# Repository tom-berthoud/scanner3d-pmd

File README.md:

# Scanner 3D — donner une forme numérique au réel

<p align="center">
  <strong>Un scanner 3D open source, compact et low-cost, conçu autour d'un Raspberry Pi.</strong><br>
  Numérisez un objet, reconstruisez sa géométrie et exportez un modèle STL prêt à être réutilisé.
</p>

<p align="center">
  <a href="assets/photo/poster_Scanner_3D.pdf">Voir le poster du projet</a> ·
  <a href="docs/rapport/">Lire le rapport complet</a>
</p>

---

## Le projet en une phrase

Scanner 3D transforme un objet posé sur un plateau rotatif en un modèle numérique exploitable grâce à une ligne laser, deux caméras et une chaîne logicielle complète — de la capture au maillage STL.

## De l'objet au modèle 3D

1. L'objet est placé au centre du plateau.
2. Le plateau effectue une rotation progressive sur 360°.
3. À chaque position, le laser dessine un profil lumineux et les deux caméras capturent la scène.
4. La ligne laser est détectée puis convertie en profil 3D par triangulation.
5. Les profils sont fusionnés en nuage de points, filtrés et transformés en maillage.
6. Le résultat est visualisable dans l'interface et exportable en STL ou OBJ.

## Pourquoi ce scanner ?

- **Accessible** — une architecture low-cost pensée pour un budget d'environ 300 CHF.
- **Autonome** — boîtier fermé, plateau motorisé, laser, caméras et écran tactile réunis dans un seul système.
- **Pédagogique** — mécanique, électronique, vision, géométrie 3D et interface web dans un même projet.
- **Pratique** — un parcours de scan simple, avec aperçu, suivi de progression et téléchargement du résultat.
- **Reproductible** — configuration YAML, calibration guidée, simulation hardware et tests automatisés.

## Une architecture complète

| Couche | Rôle |
| --- | --- |
| **Acquisition** | Capture synchronisée des deux caméras et commande du laser |
| **Vision** | Détection robuste de la ligne laser et réduction du bruit |
| **Géométrie** | Calibration caméra / laser, triangulation et fusion des deux vues |
| **Reconstruction** | Assemblage des profils en nuage de points puis maillage |
| **Interface** | Pilotage web, aperçu caméra, progression en temps réel et viewer 3D |
| **Matériel** | Raspberry Pi, moteur pas à pas, plateau rotatif, double caméra et écran local |

## Résultats

Le prototype répond aux objectifs du projet :

- acquisition d'un profil 3D à chaque rotation ;
- fusion des profils en nuage de points ;
- génération d'un maillage STL imprimable ;
- pilotage depuis une interface web Raspberry Pi ;
- fonctionnement dans une boîte fermée pour maîtriser la lumière ambiante ;
- objets ciblés jusqu'à environ **150 × 150 × 150 mm** et scan visé en moins de **10 minutes**.

Les raccourcis de déploiement, la calibration, le lancement sur Raspberry Pi et les routes de l'API sont documentés dans [README-technique.md](README-technique.md).

## Explorer les ressources

- [Poster de présentation](assets/photo/poster_Scanner_3D.pdf) — la synthèse visuelle du projet.
- [Rapport complet](docs/rapport/) — conception mécanique, électronique, logicielle et résultats.
- [Conception mécanique](docs/conceptionmecanique/) — pièces, assemblages, DXF et STL.
- [Schéma électronique](docs/schema/) — schéma et PCB KiCad.
- [Procédure de connexion](docs/connection_procedure.md) — relier le PC au Raspberry Pi.
- [Assets du projet](assets/photo/) — photos du prototype, captures d'écran et résultats 3D.

## L'équipe

Projet multidisciplinaire PMD — HEIG-VD, 2026

**[Tom Berthoud](https://github.com/tom-berthoud) · [Jason Weber](https://github.com/Jzn-wbr) · [Luc Marchand](https://github.com/luc-marchand) · [Tim Stamm](https://github.com/timstamm19) · [Hadrien Fuentes](https://github.com/hadrien-fuentes)**

Sous la responsabilité de **Cédric Bornand**.

> Projet étudiant : le scanner est un prototype expérimental. Le laser doit rester éteint lorsque le boîtier est ouvert et ne doit jamais être regardé directement.

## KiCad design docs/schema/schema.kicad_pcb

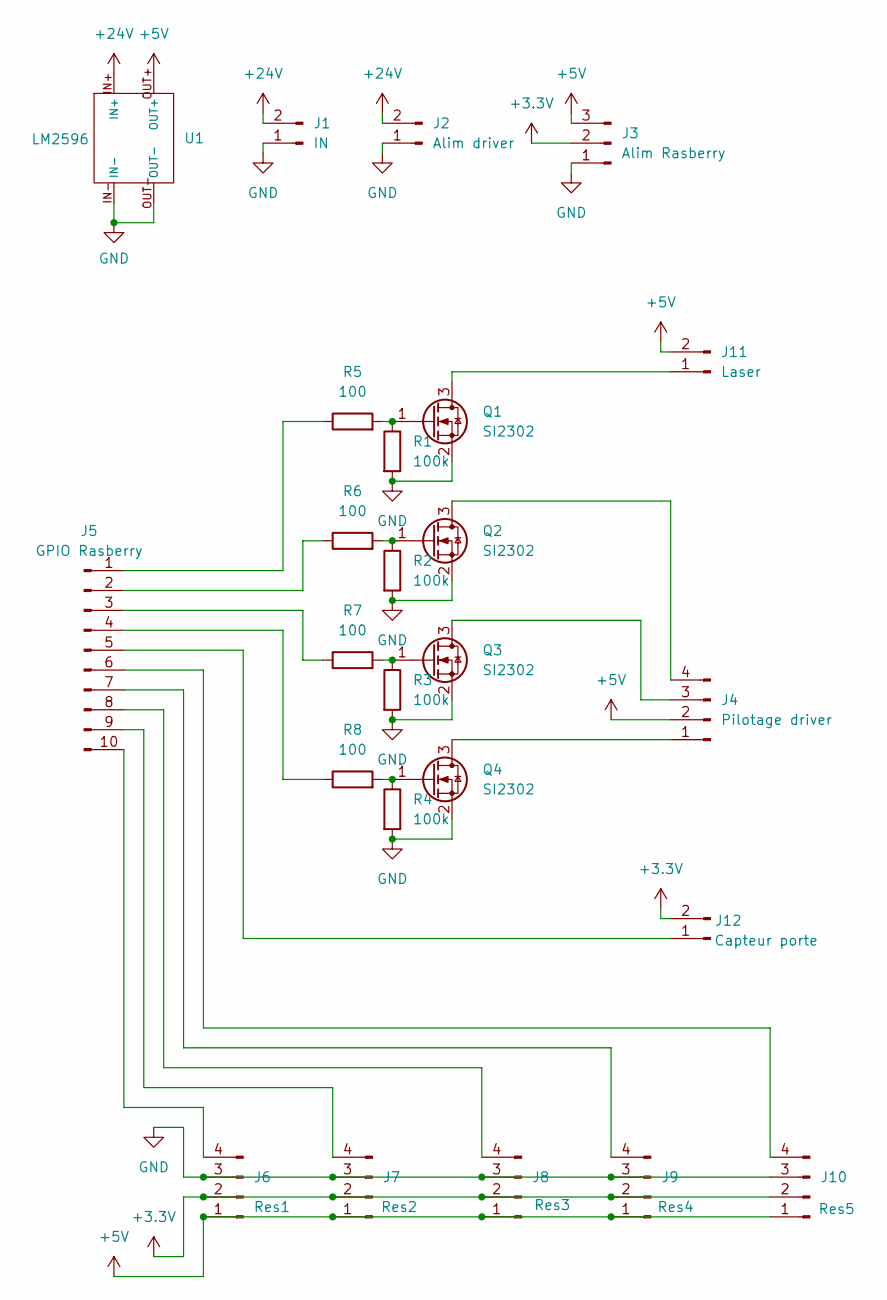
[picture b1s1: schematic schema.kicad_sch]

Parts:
J1: IN; PinHeader_1x02_P2.54mm_Vertical
J2: Alim driver; PinHeader_1x02_P2.54mm_Vertical
J3: Alim Rasberry; PinHeader_1x03_P2.54mm_Vertical
J4: Pilotage driver; PinHeader_1x04_P2.54mm_Vertical
J5: GPIO Rasberry; PinHeader_1x10_P2.54mm_Vertical
J6: Res1; PinHeader_1x04_P2.54mm_Vertical
J7: Res2; PinHeader_1x04_P2.54mm_Vertical
J8: Res3; PinHeader_1x04_P2.54mm_Vertical
J9: Res4; PinHeader_1x04_P2.54mm_Vertical
J10: Res5; PinHeader_1x04_P2.54mm_Vertical
J11: Laser; PinHeader_1x02_P2.54mm_Vertical
J12: Capteur porte; PinHeader_1x02_P2.54mm_Vertical
Q1, Q2, Q3, Q4: SI2302; SOT-23
R1, R2, R3, R4: 100k; R_1206_3216Metric
R5, R6, R7, R8: 100; R_1206_3216Metric
U1: LM2596; LM2596 module

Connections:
+3.3V: J3.2, J6.2, J7.2, J8.2, J9.2, J10.2, J12.2
+5V: J3.3, J4.2, J6.1, J7.1, J8.1, J9.1, J10.1, J11.2, U1.OUT+
+24V: J1.2, J2.2, U1.IN+
GND: J1.1, J2.1, J3.1, J6.3, J7.3, J8.3, J9.3, J10.3, Q1.2 (S), Q2.2 (S), Q3.2 (S), Q4.2 (S), R1.2, R2.2, R3.2, R4.2, U1.IN-, U1.OUT-
unnamed: J4.1, Q4.3 (D)
unnamed: J4.3, Q3.3 (D)
unnamed: J4.4, Q2.3 (D)
unnamed: J5.1, R5.1
unnamed: J5.2, R6.1
unnamed: J5.3, R7.1
unnamed: J5.4, R8.1
unnamed: J5.7, J9.4
unnamed: J5.8, J8.4
unnamed: J5.9, J7.4
unnamed: J5.10, J6.4
unnamed: J5.6, J10.4
unnamed: J11.1, Q1.3 (D)
unnamed: J5.5, J12.1
unnamed: Q1.1 (G), R1.1, R5.2
unnamed: Q2.1 (G), R2.1, R6.2
unnamed: Q3.1 (G), R3.1, R7.2
unnamed: Q4.1 (G), R4.1, R8.2

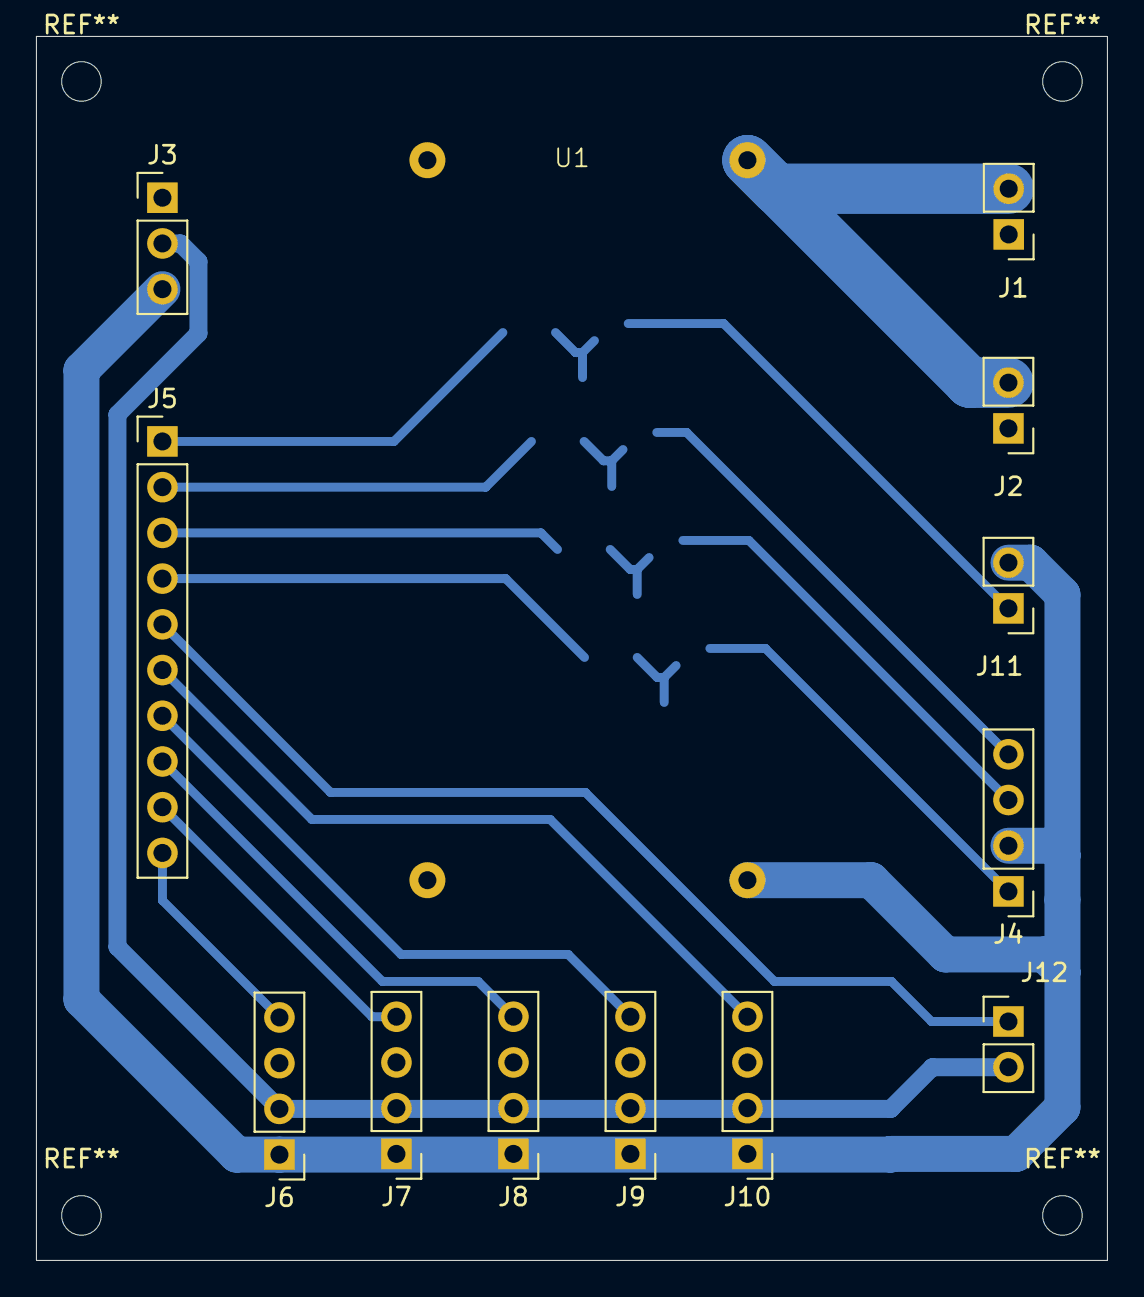
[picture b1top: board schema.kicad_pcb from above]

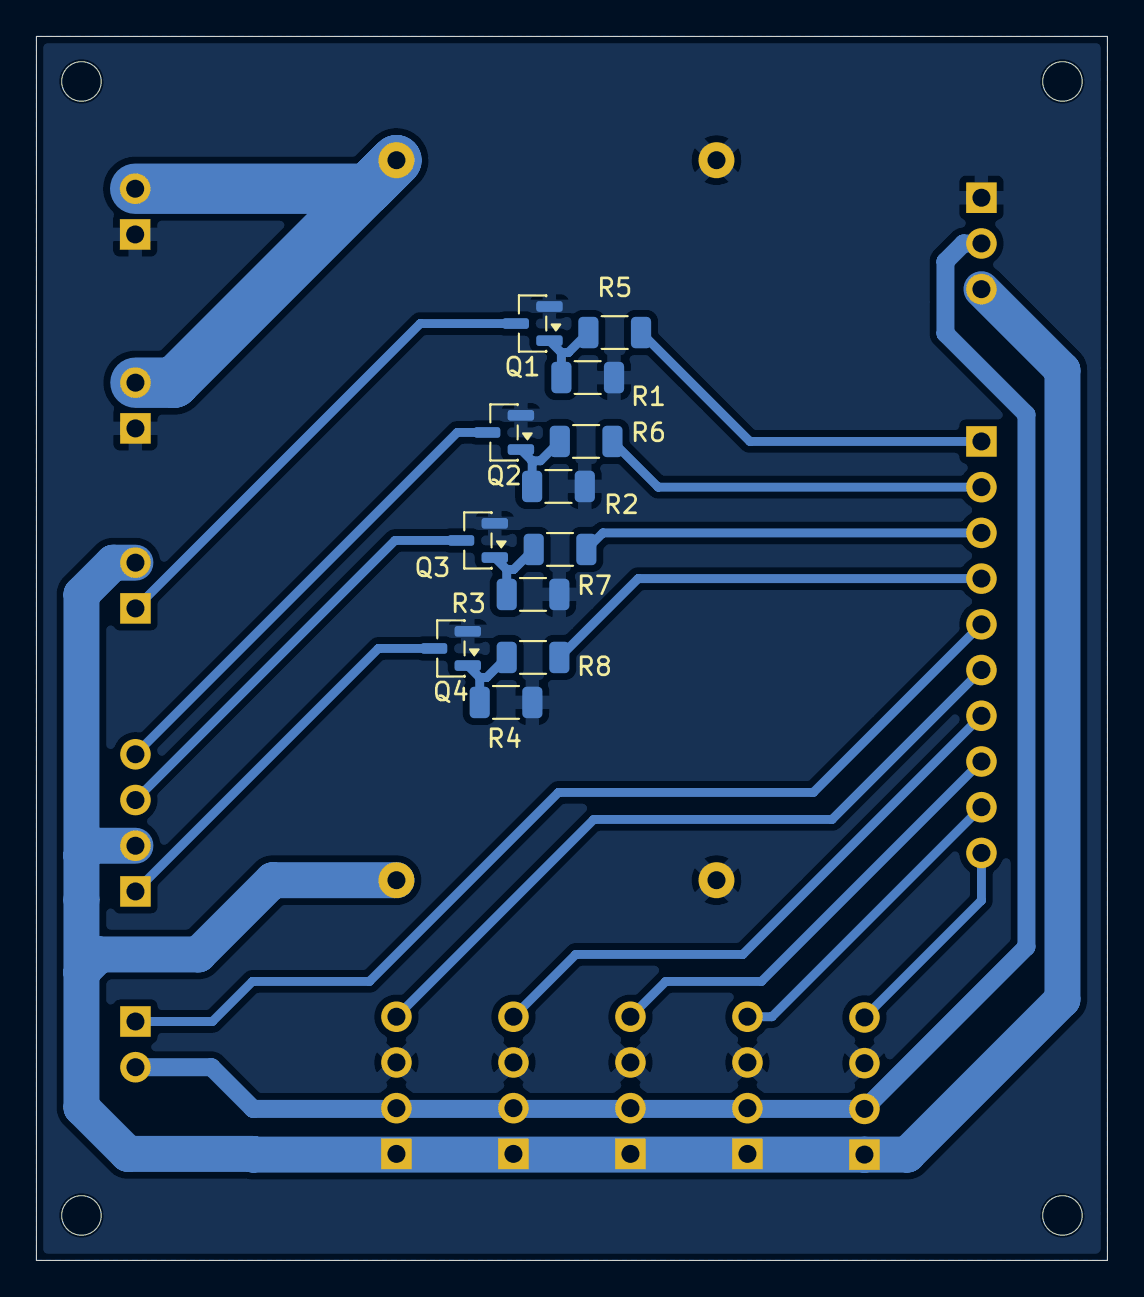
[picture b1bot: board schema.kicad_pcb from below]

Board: 2 copper layers, 59.5 x 68.0 mm, 25 parts (12 on the bottom side), 22 nets.

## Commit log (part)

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2026-04-22 rpi2
2026-04-22 rapport et scanner
2026-04-22 V1 rapport
2026-04-22 rapport
2026-04-22 add assets
2026-04-22 amelioration rapport
2026-04-22 debug
2026-04-22 asdf
2026-04-22 tuning box
2026-04-22 rpi3*
2026-04-22 tunin live 2
2026-04-22 only green
2026-04-22 only green deb
2026-04-22 codex refactor
2026-04-23 debug work
2026-04-23 calib background
2026-04-23 interpol
2026-04-23 deinterpol
2026-04-27 Update intermediate report
2026-04-27 little change, space, name
2026-04-28 presentation intermediaire v1
2026-04-28 modification conception mécanique
2026-04-28 change abreviation
2026-04-28 change intro
2026-04-28 Improve slides
2026-04-28 abréviation MDF, PLA
2026-04-28 docs: amélioration chapitre conception électronique et alimentation
    - Ajout nouvelle section 3.2 sur l'alimentation électrique avec schéma
    - Ajout subsection 3.3.1 sur l'étage de commande des GPIO avec explication technique
    - Mise à jour des signaux du driver moteur (Ena, Dir, Pull au lieu de Step/Dir)
    - Modification interface écran: DSI au lieu de HDMI/USB
    - Retrait LEDs de la table des composants (signalisation déléguée à l'état)
    - Renommage interface locale de 'Écran tactile 7 pouces' à 'Pi Touch Display 2'
2026-04-28 Report compilated
2026-04-28 photo
2026-04-28 move image and modify gitignore
2026-04-28 correction dans la présentation
2026-04-28 little change
2026-04-28 ajout du slide, voir si ok
2026-04-29 Add conception electrique
2026-04-29 add planning
2026-05-01 poisson v2
2026-05-01 TODO
2026-05-01 poisson v3
2026-05-01 poisson v4
2026-05-01 poisson v5
2026-05-02 Update manual config
2026-05-02 Update settings
2026-05-03 config fixed
2026-05-03 Extrinseque calibrated
2026-05-03 setting rasp
2026-05-03 dicrease step number
2026-05-03 No cap
2026-05-03 Update exposure cam nappe
2026-05-03 Update config
2026-05-06 Meilleur interface pour la calibration de la distortion de la lentille
2026-05-06 Add KiCAD Schema
2026-05-07 WIP: Schema
2026-05-13 Draw PCB schematic
2026-05-20 PCB designed
2026-05-20 Update PCB files
2026-05-21 Add PCB connector schema
2026-05-21 scanner: add dual camera pipeline
2026-05-21 interface: add dual camera scan artifacts viewer
2026-05-23 Ajout de la procédure de connexion et d'exécution dans le fichier connection_procedure.md
2026-05-23 Ajout de la procédure de connexion et d'exécution pour Windows.
2026-05-23 interface: prepare double camera scan workflow
2026-05-23 interface: add camera config tuning page
2026-05-23 hardware: improve usb camera runtime controls
2026-05-23 hardware: harden usb camera v4l2 controls
2026-05-23 hardware: align arducam defaults with v4l2 modes
2026-05-23 config: set tuned double camera parameters
2026-05-23 hardware: tolerate delayed usb camera startup
2026-05-23 processing: simplify laser line extraction
2026-05-23 interface: add manual processing tuning
2026-05-24 hardware: improve USB camera recovery
2026-05-24 processing: scope background crop to camera
2026-05-24 processing: remove obsolete background filter
2026-05-24 interface: add visual camera mask editor
2026-05-24 interface: support multiple polygon camera masks
2026-05-24 processing: snap camera masks to image edges
2026-05-24 interface: show snapped mask edge coordinates
2026-05-24 config: add calibrated camera masks
2026-05-24 processing: reduce mask edge snap tolerance
2026-05-24 config: update right camera trapezoid mask
2026-05-24 config: update left camera right-edge mask
2026-05-24 docs: update double-camera setup todo
2026-05-24 interface: add per-camera calibration workflow
2026-05-24 config: set USB camera to 1080p
2026-05-24 config: update USB camera mask
2026-05-24 interface: add camera calibration exposure controls
2026-05-24 docs: add printable calibration checkerboard
2026-05-24 calibration: report camera calibration errors
2026-05-24 config: enable checkerboard intrinsics
2026-05-24 config: add camera intrinsics calibration
2026-05-24 config: reduce right camera scan exposure
2026-05-24 config: track camera intrinsics files
2026-05-24 config: clarify platform coordinate frame
2026-05-24 calibration: support vertical laser reference board
2026-05-24 interface: guide dual-camera laser calibration
2026-05-24 config: add calibrated laser planes
2026-05-24 docs: update setup calibration checklist
2026-05-25 calibration: use shared global laser plane
2026-05-25 config: update global laser plane calibration
2026-05-25 Try theorical laser plane
2026-05-25 processing: add laser line sampling
2026-05-25 Fix wrong cote
2026-05-25 calibration: add checkerboard extrinsics workflow
2026-05-25 calibration: guard extrinsics pose selection
2026-05-25 calibration: add turntable extrinsics calibration
2026-05-25 calibration: automate turntable extrinsics captures
2026-05-25 calibration: remove extrinsics calibration workflow
2026-05-25 calibration: support mechanical angle extrinsics
2026-05-25 Try invert settings
2026-05-25 calibration: add ArUco cube extrinsics workflow
2026-05-25 calibration: auto-select ArUco cube layout
2026-05-25 calibration: estimate ArUco cube angle offset
2026-05-25 Revert "calibration: auto-select ArUco cube layout"
    This reverts commit b35d39b862c626702fe6430db8cf9b53e6b2a0f1.
2026-05-25 Revert "calibration: estimate ArUco cube angle offset"
    This reverts commit bc08a64754e82f805513dc43590bdfa3b0723649.
2026-05-25 calibration: remove ArUco cube extrinsics workflow
2026-05-25 Calibrate manually
2026-05-25 config: restore clean manual settings
2026-05-25 Resolve angle imprecision
2026-05-25 Extrinseque left cam
2026-05-25 interface: add manual extrinsics tuning view
2026-05-25 interface: speed up extrinsics capture
2026-05-25 interface: add extrinsics 3d reference grid
2026-05-26 Add debug
2026-05-26 Add offset
2026-05-26 processing: add per-camera scale_xyz and cube scale estimator script
2026-05-26 config: add left camera scale_xyz from cube matching
2026-05-26 processing: add pixel_ratio-based laser sampling across pipeline
2026-05-26 test fix claude
2026-05-26 interface: add extrinsics cheat mode auto-fit between cameras
2026-05-26 interface: make cheat mode optimize both cameras from cached extracted points
2026-05-27 fix initialisation usb
2026-05-27 ajout des poster et presentation finale
2026-05-27 reconstruction: add aligned flat caps completion before mesh export
2026-05-27 orchestration: run auto extrinsics cheat before triangulation
2026-05-27 modificationdes suivi de fichier
2026-05-28 processing: fuse dual-camera profiles by continuous segments per angle
2026-05-28 processing: add local polynomial regression on continuous profile segments
2026-05-29 modification des GPIO et ajout de l'interlock
2026-05-30 hardware: make LEDs optional and disable them in settings
2026-05-30 interface: add processing step timeline and door interlock status
2026-05-30 safety: switch door interlock GPIO10 to pull-down
2026-05-30 safety: force laser off immediately on door open
2026-05-30 processing: make dual-profile fusion conservative in overlap
2026-05-30 reconstruction: switch to single flat bottom cap and enable flat_caps
2026-05-30 reconstruction: place bottom cap on world-Y plane (XZ footprint)
2026-05-30 meilleur vue
2026-05-30 fix mock
2026-05-30 ajout image heig-vd
2026-05-30 ajout animation et meilleur ui
2026-05-31 interface: update USB camera laser mask trapezoid
2026-05-31 meilleur animation et logo heig-vd
2026-05-31 test fix
2026-05-31 Update Arducam mask
2026-05-31 interface: filter extrinsics fit points by 2D vertical-angle gate
2026-05-31 enlever les leds
2026-06-01 fix rafraichissement
2026-06-02 config: tune nappe laser detection
2026-06-02 reconstruction: fuse half-turn duplicate profiles
2026-06-02 reconstruction: use xyz distance for half-turn fusion
2026-06-02 scan: calibrate exposure before capture
2026-06-02 scan: iterate exposure calibration until tolerance
2026-06-02 reconstruction: fuse half-turn points locally
2026-06-02 reconstruction: clip artifacts above detected top plane
2026-06-03 interface: prevent concurrent scan workers
2026-06-03 reconstruction: clip top artifacts by fitted plane
2026-06-03 reconstruction: detect dense planar top band
2026-06-03 Update density
2026-06-03 export: clip and cap mesh by top plane
2026-06-03 docs et test
2026-06-03 dernière slide
2026-06-05 Présenation finale renomée
2026-06-05 ajotu image
2026-06-05 Avancement rapport finale Partie Electrique
2026-06-05 ajout image, buget et planning
2026-06-06 ajout signatures
2026-06-07 ajout des réferences, et schema
2026-06-07 ajout signature tim
2026-06-07 modif pour mock
2026-06-07 ajout image UI final, corriger des malcomprension
2026-06-07 modif presentation final
2026-06-07 Clean old files
2026-06-07 enlever les OBJ
2026-06-07 enlever main.pdf
2026-06-07 ajout signature jason
2026-06-07 rapport biblio
2026-06-07 2eme partie chapitre 06 Ok, Attention il faut encore réglé le nettoyage que hadien a fait !
2026-06-07 pres
2026-06-07 Chapitre 06_conception_electrique Ok
2026-06-07 pres2
2026-06-07 Ajout signature luc, ne s'affiche pas correctement
2026-06-07 Ajout image signature luc
2026-06-07 ajout image presentation finale
2026-06-07 Stop tracking compiled report PDF
2026-06-07 fix signature
2026-06-07 fais du trie
2026-06-07 Ajout nouvelle version PDF + Déplacement \subsection{Mesures électriques et consommation}
2026-06-07 changement de caisson par boite et ajout des gravure
2026-06-07 details
2026-06-07 ajout image CAD
2026-06-07 modif
2026-06-07 ajout conception mec
2026-06-07 fix readme
2026-06-07 ajout lien github
2026-06-07 ajotu remerciement
2026-06-07 detail
